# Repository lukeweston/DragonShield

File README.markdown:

DragonShield v1.0

Dragino daughterboard with SPI real-time clock, socket for XBee 802.15.4 module or similar "Bee" module and micro-SD card socket.

The XBee module is simply connected to the serial UART on the AR2317.

The RTC and the micro-SD card are connected to the AR2317's GPIO pins, and an appropriate SPI interface can be implemented through an appropriate driver within the OS.

More documentation to be written in future.

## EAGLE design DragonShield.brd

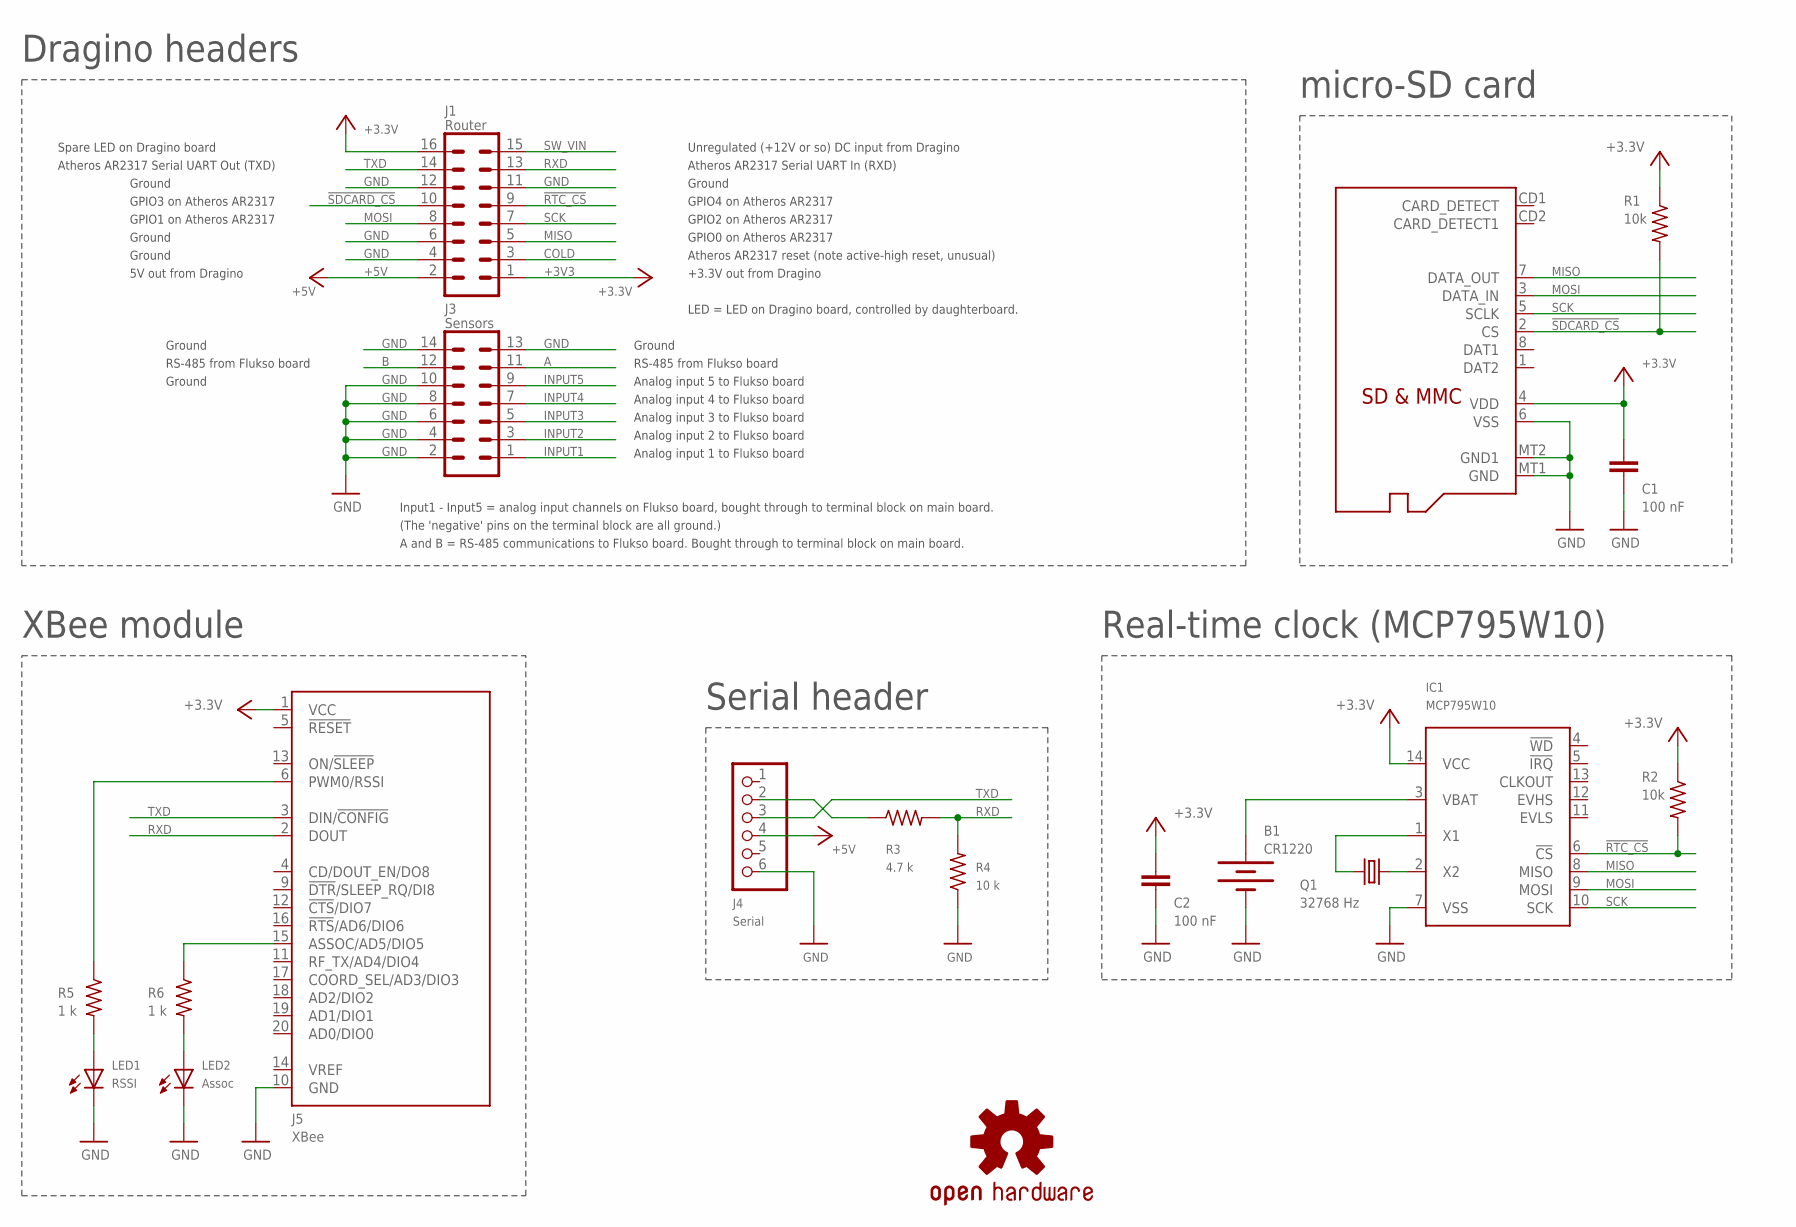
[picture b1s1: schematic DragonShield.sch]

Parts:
B1: CR1220; BATTCON_12MM
C1, C2: 100 nF; C0805K
IC1: MCP795W10; SOIC14
J1: Router; MA08-2
J2: MICROSD
J3: Sensors; MA07-2
J4: Serial; 1X06
J5: XBee; XBEE-PRO
LED1: RSSI; LED-0805-LARGE
LED2: Assoc; LED-0805-LARGE
Q1: 32768 Hz; TC26H
R1, R2: 10k; M0805
R3: 4.7 k; M0805
R4: 10 k; M0805
R5, R6: 1 k; M0805
U$: OSHW-LOGOS; OSHW-LOGO-S

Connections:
!RTC_CS: IC1.6 (!CS), J1.9, R2.2
!SDCARD_CS: J1.10, J2.2 (CS), R1.2
+3V3: C1.2, C2.2, IC1.14 (VCC), J1.1, J1.16, J2.4 (VDD), J5.1 (VCC), R1.1, R2.1
+5V: J1.2, J4.4
A: J3.11
B: J3.12
COLD: J1.3
GND: B1.GND (-), C1.1, C2.1, IC1.7 (VSS), J1.4, J1.6, J1.11, J1.12, J2.6 (VSS), J2.MT1 (GND), J2.MT2 (GND1), J3.2, J3.4, J3.6, J3.8, J3.10, J3.13, J3.14, J4.6, J5.10 (GND), LED1.C, LED2.C, R4.1
INPUT1: J3.1
INPUT2: J3.3
INPUT3: J3.5
INPUT4: J3.7
INPUT5: J3.9
MISO: IC1.8 (MISO), J1.5, J2.7 (DATA_OUT)
MOSI: IC1.9 (MOSI), J1.8, J2.3 (DATA_IN)
unnamed: J4.2, R3.1
unnamed: IC1.1 (X1), Q1.2
unnamed: IC1.2 (X2), Q1.1
unnamed: LED2.A, R6.2
unnamed: J5.15 (ASSOC/AD5/DIO5), R6.1
unnamed: LED1.A, R5.2
unnamed: J5.6 (PWM0/RSSI), R5.1
unnamed: B1.PWR@1 (+), IC1.3 (VBAT)
RXD: J1.13, J5.2 (DOUT), R3.2, R4.2
SCK: IC1.10 (SCK), J1.7, J2.5 (SCLK)
SW_VIN: J1.15
TXD: J1.14, J4.3, J5.3 (DIN/!CONFIG)

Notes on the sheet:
A and B = RS-485 communications to Flukso board. Bought through to terminal block on main board.
Input1 - Input5 = analog input channels on Flukso board, bought through to terminal block on main board.
(The 'negative' pins on the terminal block are all ground.)
RS-485 from Flukso board
Analog input 5 to Flukso board
+3.3V out from Dragino
GPIO0 on Atheros AR2317
GPIO2 on Atheros AR2317
GPIO4 on Atheros AR2317
GPIO3 on Atheros AR2317
GPIO1 on Atheros AR2317
5V out from Dragino
Analog input 4 to Flukso board
Analog input 3 to Flukso board
Analog input 2 to Flukso board
Analog input 1 to Flukso board
Spare LED on Dragino board
Atheros AR2317 Serial UART Out (TXD)
Atheros AR2317 Serial UART In (RXD)
Unregulated (+12V or so) DC input from Dragino
Atheros AR2317 reset (note active-high reset, unusual)
Ground
LED = LED on Dragino board, controlled by daughterboard.
Dragino headers
XBee module
Real-time clock (MCP795W10)
micro-SD card
Serial header

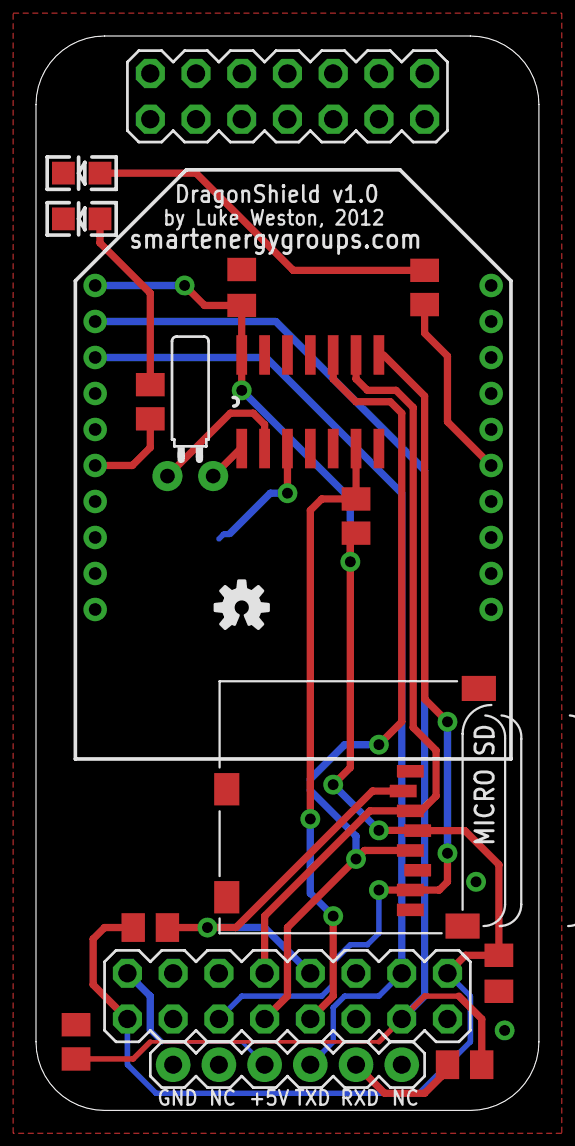
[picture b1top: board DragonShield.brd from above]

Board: 2 copper layers, 27.9 x 59.7 mm, 19 parts (1 on the bottom side), 18 nets.

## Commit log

2012-04-03 added serial header
2012-04-04 fixed mask DRC errors
